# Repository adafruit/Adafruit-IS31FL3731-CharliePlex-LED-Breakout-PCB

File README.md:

## Adafruit IS31FL3731 CharliePlex LED Breakout PCB
<a href="http://www.adafruit.com/products/2946"><br/>
Click here to purchase one from the Adafruit shop</a>

The IS31FL3731 will let you get back to that classic LED matrix look, with a nice upgrade! This I2C LED driver chip has the ability to PWM each individual LED in a 16x9 grid so you can have beautiful LED lighting effects, without a lot of pin twiddling. Simply tell the chip which LED on the grid you want lit, and what brightness and it's all taken care of for you.

The IS31FL3731 is a nice little chip - it can use 2.7-5.5V power and logic so its flexible for use with any microcontroller. You can set the address so up to 4 matrices can share an I2C bus. Inside is enough RAM for 8 seperate frames of display memory so you can set up multiple frames of an animation and flip them to be displayed with a single command.

This chip is great for making small LED displays, and we even designed the breakout to match up with our ready-to-go LED grids in red, yellow, green, blue and white. Sandwich the driver and matrix breakout, solder together for a compact setup. Or you can DIY your own setup, just follow the LED grid schematic in the IS31FL3731 datasheet.

To get you going fast, we spun up a custom-made PCB in the STEMMA QT form factor, making it easy to interface with. The STEMMA QT connectors on either side are compatible with the SparkFun Qwiic I2C connectors. This allows you to make solderless connections between your development board and the IS31FL3731 or to chain it with a wide range of other sensors and accessories using a compatible cable. The IS31 is compatible with 3-5V power and logic, so it's ready to go with just about any microcontroller or microcomputer board!

Please note this does not come with any LEDs, you can pick up a matching LED matrix from us or DIY your own.

Pick up a driver board and your favorite color LEDs to match. You'll need to do some basic soldering to attach the driver backpack and matrix together, and run wires to your microcontroller, but its not too hard. Then install our Arduino or CircuitPython libraries to get some LEDs blinking immediately. Our library is Adafruit_GFX compatible so you can draw lines, circles, text, and small bitmaps if you want more graphics control

Check out our detailed tutorial for Arduino & CircuitPython support, pinouts, assembly, wiring, and more!

See the following products for various flavors of this product:

- https://www.adafruit.com/products/2946 (the IS31FL breakout)
- https://www.adafruit.com/products/2973 (blue LEDs)
- https://www.adafruit.com/products/2974 (cool white LEDs)
- https://www.adafruit.com/products/2948 (yellow LEDs)
- https://www.adafruit.com/products/2947 (red LEDs)
- https://www.adafruit.com/products/2972 (green LEDs)

PCB files for the IS31FL3731 CharliePlex LED Breakouts. The format is EagleCAD schematic and board layout

### License

Adafruit invests time and resources providing this open source design, please support Adafruit and open-source hardware by purchasing products from [Adafruit](https://www.adafruit.com)!

All text above must be included in any redistribution

Designed by Limor Fried/Ladyada for Adafruit Industries.
Creative Commons Attribution/Share-Alike, all text above must be included in any redistribution. 
See license.txt for additional information.

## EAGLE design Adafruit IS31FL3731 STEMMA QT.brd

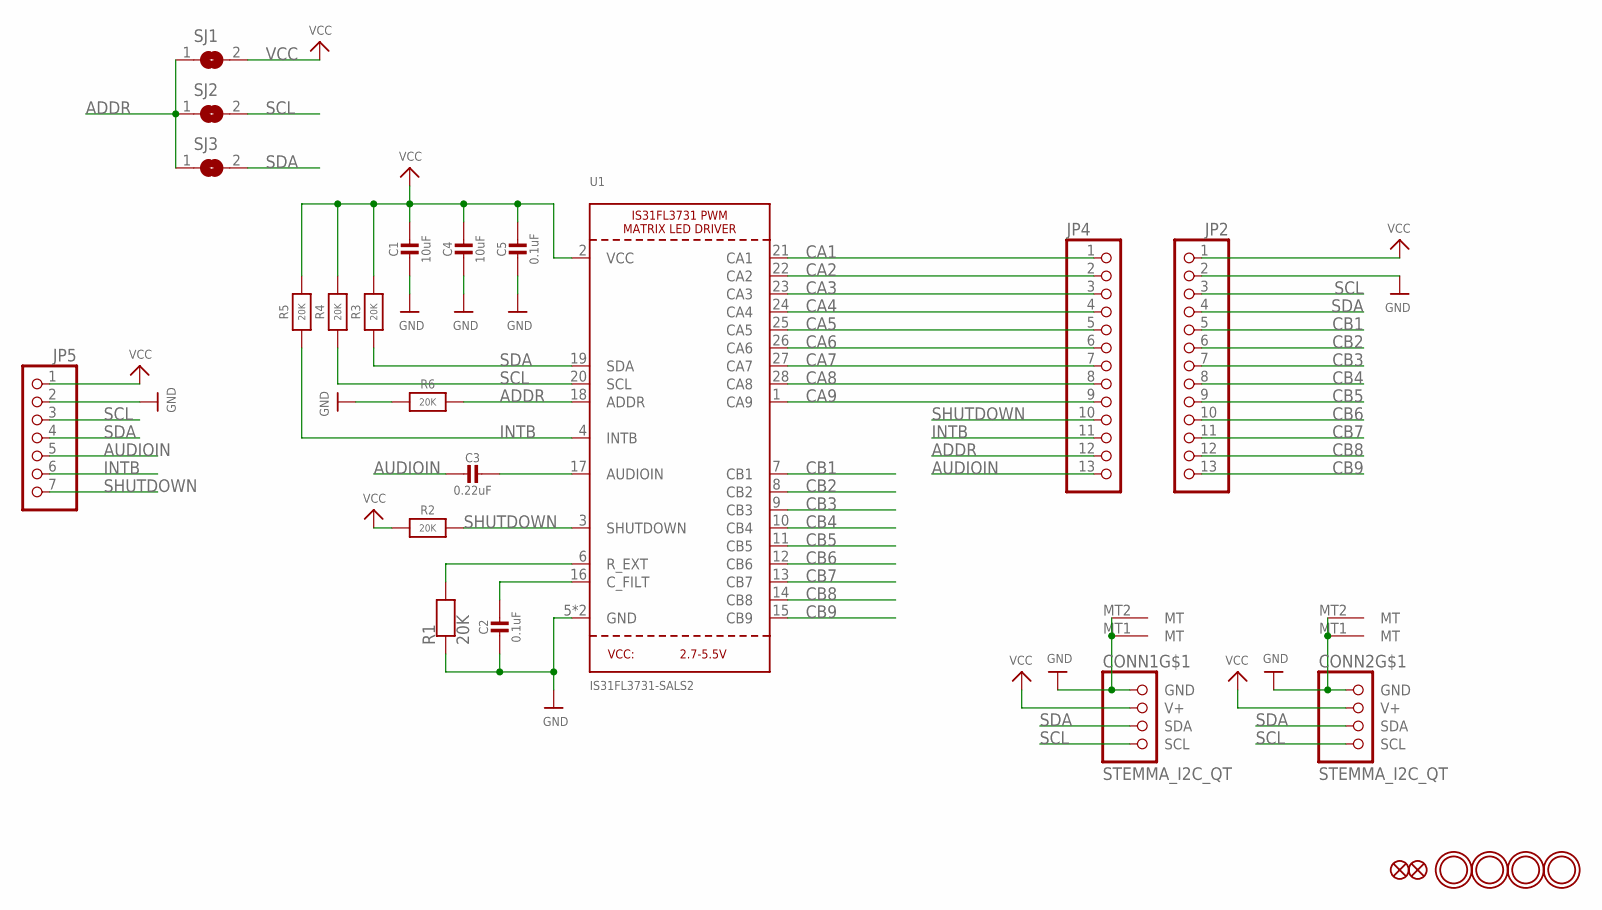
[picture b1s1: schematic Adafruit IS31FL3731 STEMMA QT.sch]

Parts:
C1, C4: 10uF; 0805-NO
C2, C5: 0.1uF; 0603-NO
C3: 0.22uF; 0603-NO
CONN1, CONN2: STEMMA_I2C_QT; JST_SH4
FID1, FID2: FIDUCIAL_1MM
JP2, JP4: HEADER-1X13; 1X13_ROUND_70
JP5: HEADER-1X7THICKER; 1X07_ROUND_76
R1: 20K; 0603-THM
R2, R3, R4, R5, R6: 20K; 0603-NO
SJ1, SJ2, SJ3: SOLDERJUMPER; SOLDERJUMPER_ARROW_NOPASTE
U1: IS31FL3731-SALS2; QFN28_4MM_0.4MM
U$3, U$4, U$5, U$6: MOUNTINGHOLE2.5; MOUNTINGHOLE_2.5_PLATED

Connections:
ADDR: JP4.12, R6.2, SJ1.1, SJ2.1, SJ3.1, U1.18 (ADDR)
AUDIOIN: C3.2, JP4.13, JP5.5
CA1: JP4.1, U1.21 (CA1)
CA2: JP4.2, U1.22 (CA2)
CA3: JP4.3, U1.23 (CA3)
CA4: JP4.4, U1.24 (CA4)
CA5: JP4.5, U1.25 (CA5)
CA6: JP4.6, U1.26 (CA6)
CA7: JP4.7, U1.27 (CA7)
CA8: JP4.8, U1.28 (CA8)
CA9: JP4.9, U1.1 (CA9)
CB1: JP2.5, U1.7 (CB1)
CB2: JP2.6, U1.8 (CB2)
CB3: JP2.7, U1.9 (CB3)
CB4: JP2.8, U1.10 (CB4)
CB5: JP2.9, U1.11 (CB5)
CB6: JP2.10, U1.12 (CB6)
CB7: JP2.11, U1.13 (CB7)
CB8: JP2.12, U1.14 (CB8)
CB9: JP2.13, U1.15 (CB9)
GND: C1.2, C2.2, C4.2, C5.2, CONN1.1 (GND), CONN1.MT1 (MT), CONN1.MT2 (MT), CONN2.1 (GND), CONN2.MT1 (MT), CONN2.MT2 (MT), JP2.2, JP5.2, R1.1, R1.11 (1), R6.1, U1.5 (GND), U1.THERMAL (GND)
INTB: JP4.11, JP5.6, R5.1, U1.4 (INTB)
unnamed: C2.1, U1.16 (C_FILT)
unnamed: C3.1, U1.17 (AUDIOIN)
REXT: R1.2, R1.22 (2), U1.6 (R_EXT)
SCL: CONN1.4 (SCL), CONN2.4 (SCL), JP2.3, JP5.3, R4.1, SJ2.2, U1.20 (SCL)
SDA: CONN1.3 (SDA), CONN2.3 (SDA), JP2.4, JP5.4, R3.1, SJ3.2, U1.19 (SDA)
SHUTDOWN: JP4.10, JP5.7, R2.2, U1.3 (SHUTDOWN)
VCC: C1.1, C4.1, C5.1, CONN1.2 (V+), CONN2.2 (V+), JP2.1, JP5.1, R2.1, R3.2, R4.2, R5.2, SJ1.2, U1.2 (VCC)

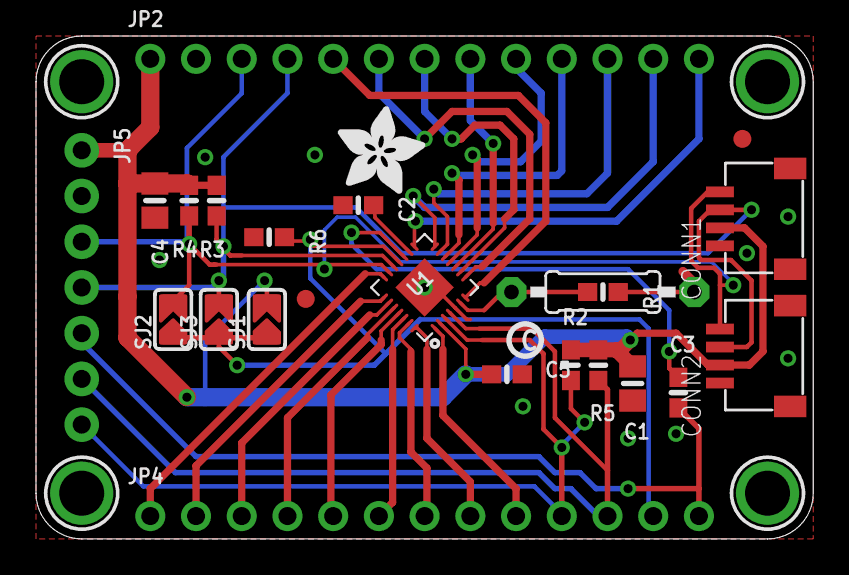
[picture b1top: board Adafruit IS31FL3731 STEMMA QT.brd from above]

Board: 2 copper layers, 43.2 x 27.9 mm, 68 parts (0 on the bottom side), 29 nets.

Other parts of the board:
PLABEL0: PLABEL0
PLABEL1: PLABEL1
PLABEL2: PLABEL2
PLABEL3: PLABEL3
PLABEL4: PLABEL4
PLABEL5: PLABEL5
PLABEL6: PLABEL6
PLABEL7: PLABEL7
PLABEL8: PLABEL8
PLABEL9: PLABEL9
PLABEL10: PLABEL10
PLABEL11: PLABEL11
PLABEL12: PLABEL12
PLABEL13: PLABEL13
PLABEL14: PLABEL14
PLABEL15: PLABEL15
PLABEL16: PLABEL16
PLABEL17: PLABEL17
PLABEL18: PLABEL18
PLABEL19: PLABEL19
PLABEL20: PLABEL20
PLABEL21: PLABEL21
PLABEL22: PLABEL22
PLABEL23: PLABEL23
PLABEL24: PLABEL24
PLABEL25: PLABEL25
PLABEL26: PLABEL26
PLABEL27: PLABEL27
PLABEL28: PLABEL28
PLABEL29: PLABEL29
PLABEL30: PLABEL30
PLABEL31: PLABEL31
PLABEL32: PLABEL32
PLABEL33: PLABEL33
PLABEL34: PLABEL34
PLABEL35: PLABEL35
PLABEL36: PLABEL36
PLABEL37: PLABEL37
PLABEL38: PLABEL38
PLABEL39: PLABEL39
U$10: ADAFRUIT_5MM
U$11: PCBFEAT-REV-040

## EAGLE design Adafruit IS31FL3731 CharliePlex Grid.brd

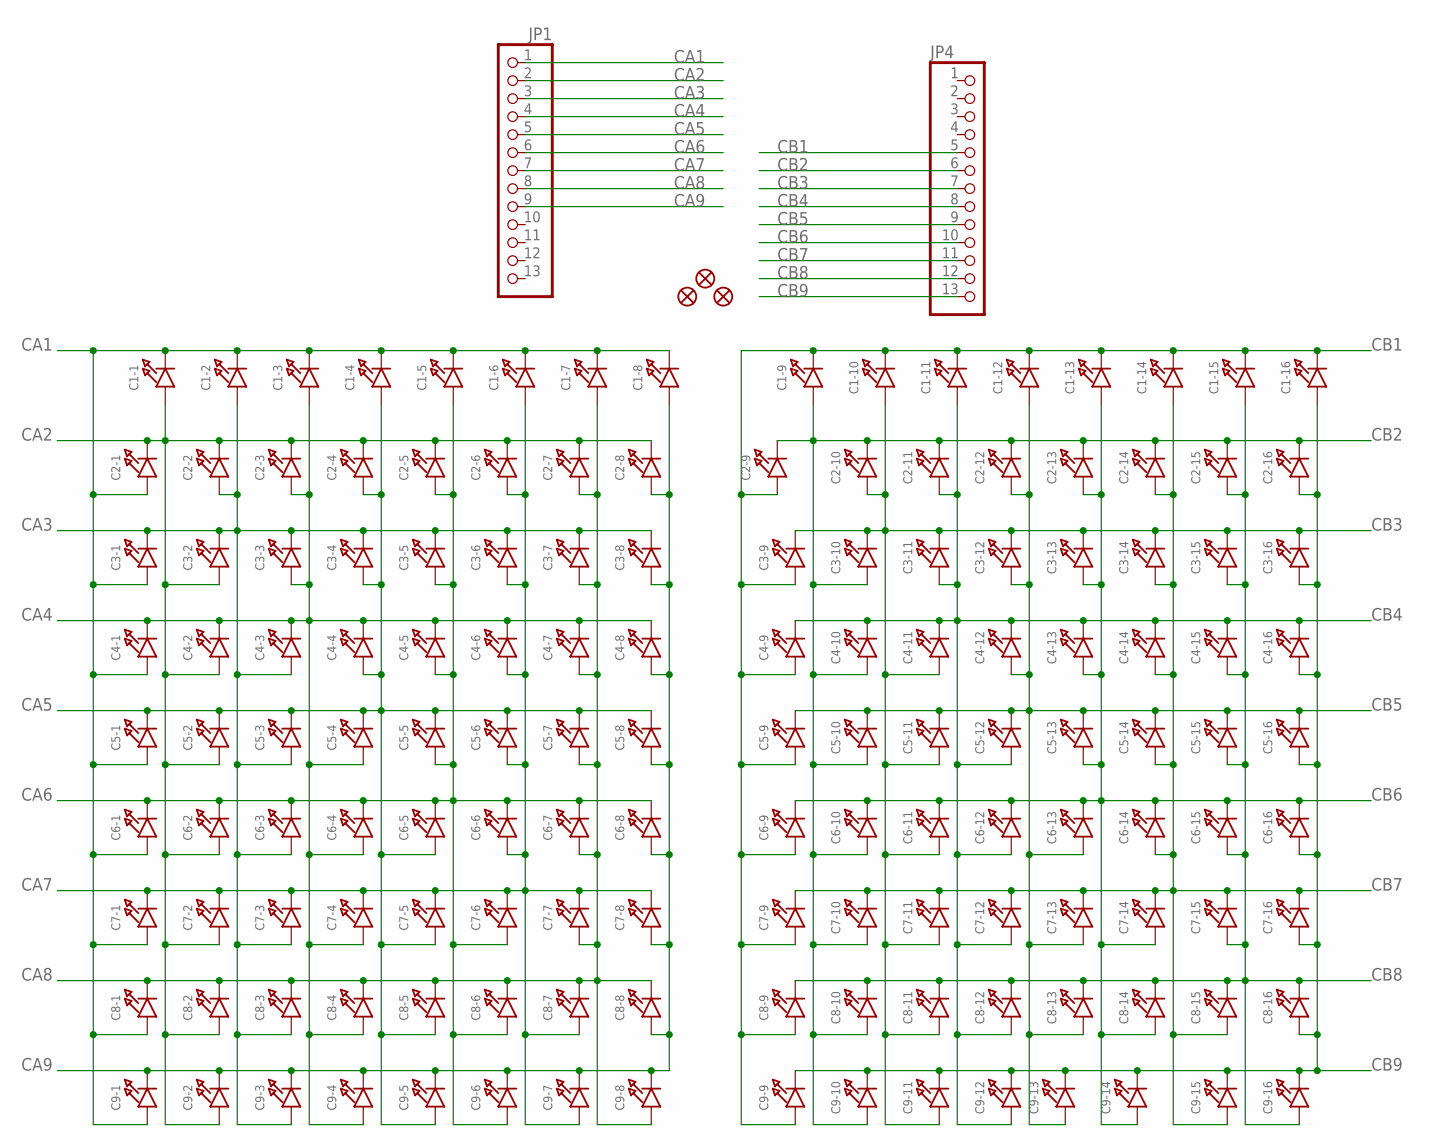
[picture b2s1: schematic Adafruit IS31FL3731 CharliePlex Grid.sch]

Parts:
C1-1, C1-2, C1-3, C1-4, C1-5, C1-6, C1-7, C1-8, C1-9, C1-10, C1-11, C1-12, C1-13, C1-14, C1-15, C1-16, C2-1, C2-2, C2-3, C2-4, C2-5, C2-6, C2-7, C2-8, C2-9, C2-10, C2-11, C2-12, C2-13, C2-14, C2-15, C2-16, C3-1, C3-2, C3-3, C3-4, C3-5, C3-6, C3-7, C3-8, C3-9, C3-10, C3-11, C3-12, C3-13, C3-14, C3-15, C3-16, C4-1, C4-2, C4-3, C4-4, C4-5, C4-6, C4-7, C4-8, C4-9, C4-10, C4-11, C4-12, C4-13, C4-14, C4-15, C4-16, C5-1, C5-2, C5-3, C5-4, C5-5, C5-6, C5-7, C5-8, C5-9, C5-10, C5-11, C5-12, C5-13, C5-14, C5-15, C5-16, C6-1, C6-2, C6-3, C6-4, C6-5, C6-6, C6-7, C6-8, C6-9, C6-10, C6-11, C6-12, C6-13, C6-14, C6-15, C6-16, C7-1, C7-2, C7-3, C7-4, C7-5, C7-6, C7-7, C7-8, C7-9, C7-10, C7-11, C7-12, C7-13, C7-14, C7-15, C7-16, C8-1, C8-2, C8-3, C8-4, C8-5, C8-6, C8-7, C8-8, C8-9, C8-10, C8-11, C8-12, C8-13, C8-14, C8-15, C8-16, C9-1, C9-2, C9-3, C9-4, C9-5, C9-6, C9-7, C9-8, C9-9, C9-10, C9-11, C9-12, C9-13, C9-14, C9-15, C9-16: LED0603_NOOUTLINE; CHIPLED_0603_NOOUTLINE
FID1, FID2, FID3: FIDUCIAL""; FIDUCIAL_1MM
JP1, JP4: HEADER-1X13; 1X13_ROUND_70

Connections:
CA1: C1-1.C, C1-2.C, C1-3.C, C1-4.C, C1-5.C, C1-6.C, C1-7.C, C1-8.C, C2-1.A, C3-1.A, C4-1.A, C5-1.A, C6-1.A, C7-1.A, C8-1.A, C9-1.A, JP1.1
CA2: C1-1.A, C2-1.C, C2-2.C, C2-3.C, C2-4.C, C2-5.C, C2-6.C, C2-7.C, C2-8.C, C3-2.A, C4-2.A, C5-2.A, C6-2.A, C7-2.A, C8-2.A, C9-2.A, JP1.2
CA3: C1-2.A, C2-2.A, C3-1.C, C3-2.C, C3-3.C, C3-4.C, C3-5.C, C3-6.C, C3-7.C, C3-8.C, C4-3.A, C5-3.A, C6-3.A, C7-3.A, C8-3.A, C9-3.A, JP1.3
CA4: C1-3.A, C2-3.A, C3-3.A, C4-1.C, C4-2.C, C4-3.C, C4-4.C, C4-5.C, C4-6.C, C4-7.C, C4-8.C, C5-4.A, C6-4.A, C7-4.A, C8-4.A, C9-4.A, JP1.4
CA5: C1-4.A, C2-4.A, C3-4.A, C4-4.A, C5-1.C, C5-2.C, C5-3.C, C5-4.C, C5-5.C, C5-6.C, C5-7.C, C5-8.C, C6-5.A, C7-5.A, C8-5.A, C9-5.A, JP1.5
CA6: C1-5.A, C2-5.A, C3-5.A, C4-5.A, C5-5.A, C6-1.C, C6-2.C, C6-3.C, C6-4.C, C6-5.C, C6-6.C, C6-7.C, C6-8.C, C7-6.A, C8-6.A, C9-6.A, JP1.6
CA7: C1-6.A, C2-6.A, C3-6.A, C4-6.A, C5-6.A, C6-6.A, C7-1.C, C7-2.C, C7-3.C, C7-4.C, C7-5.C, C7-6.C, C7-7.C, C7-8.C, C8-7.A, C9-7.A, JP1.7
CA8: C1-7.A, C2-7.A, C3-7.A, C4-7.A, C5-7.A, C6-7.A, C7-7.A, C8-1.C, C8-2.C, C8-3.C, C8-4.C, C8-5.C, C8-6.C, C8-7.C, C8-8.C, C9-8.A, JP1.8
CA9: C1-8.A, C2-8.A, C3-8.A, C4-8.A, C5-8.A, C6-8.A, C7-8.A, C8-8.A, C9-1.C, C9-2.C, C9-3.C, C9-4.C, C9-5.C, C9-6.C, C9-7.C, C9-8.C, JP1.9
CB1: C1-9.C, C1-10.C, C1-11.C, C1-12.C, C1-13.C, C1-14.C, C1-15.C, C1-16.C, C2-9.A, C3-9.A, C4-9.A, C5-9.A, C6-9.A, C7-9.A, C8-9.A, C9-9.A, JP4.5
CB2: C1-9.A, C2-9.C, C2-10.C, C2-11.C, C2-12.C, C2-13.C, C2-14.C, C2-15.C, C2-16.C, C3-10.A, C4-10.A, C5-10.A, C6-10.A, C7-10.A, C8-10.A, C9-10.A, JP4.6
CB3: C1-10.A, C2-10.A, C3-9.C, C3-10.C, C3-11.C, C3-12.C, C3-13.C, C3-14.C, C3-15.C, C3-16.C, C4-11.A, C5-11.A, C6-11.A, C7-11.A, C8-11.A, C9-11.A, JP4.7
CB4: C1-11.A, C2-11.A, C3-11.A, C4-9.C, C4-10.C, C4-11.C, C4-12.C, C4-13.C, C4-14.C, C4-15.C, C4-16.C, C5-12.A, C6-12.A, C7-12.A, C8-12.A, C9-12.A, JP4.8
CB5: C1-12.A, C2-12.A, C3-12.A, C4-12.A, C5-9.C, C5-10.C, C5-11.C, C5-12.C, C5-13.C, C5-14.C, C5-15.C, C5-16.C, C6-13.A, C7-13.A, C8-13.A, C9-13.A, JP4.9
CB6: C1-13.A, C2-13.A, C3-13.A, C4-13.A, C5-13.A, C6-9.C, C6-10.C, C6-11.C, C6-12.C, C6-13.C, C6-14.C, C6-15.C, C6-16.C, C7-14.A, C8-14.A, C9-14.A, JP4.10
CB7: C1-14.A, C2-14.A, C3-14.A, C4-14.A, C5-14.A, C6-14.A, C7-9.C, C7-10.C, C7-11.C, C7-12.C, C7-13.C, C7-14.C, C7-15.C, C7-16.C, C8-15.A, C9-15.A, JP4.11
CB8: C1-15.A, C2-15.A, C3-15.A, C4-15.A, C5-15.A, C6-15.A, C7-15.A, C8-9.C, C8-10.C, C8-11.C, C8-12.C, C8-13.C, C8-14.C, C8-15.C, C8-16.C, C9-16.A, JP4.12
CB9: C1-16.A, C2-16.A, C3-16.A, C4-16.A, C5-16.A, C6-16.A, C7-16.A, C8-16.A, C9-9.C, C9-10.C, C9-11.C, C9-12.C, C9-13.C, C9-14.C, C9-15.C, C9-16.C, JP4.13

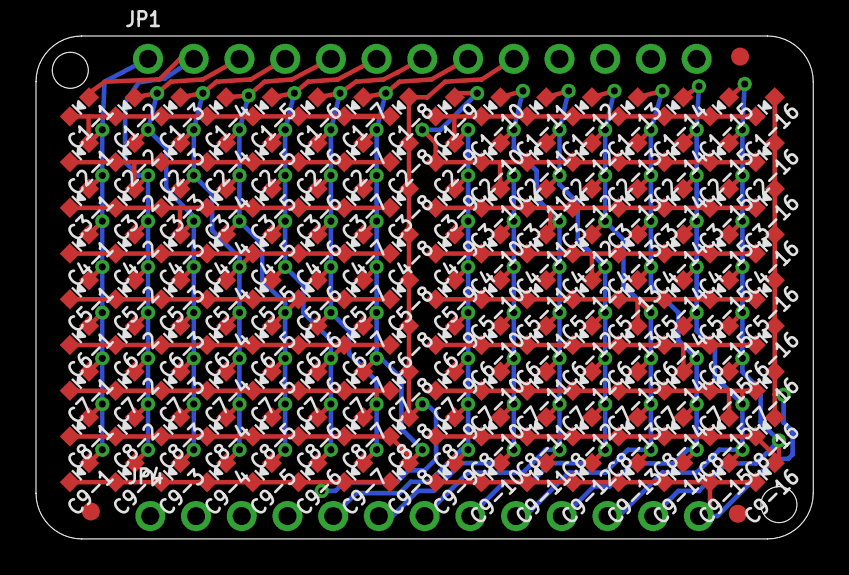
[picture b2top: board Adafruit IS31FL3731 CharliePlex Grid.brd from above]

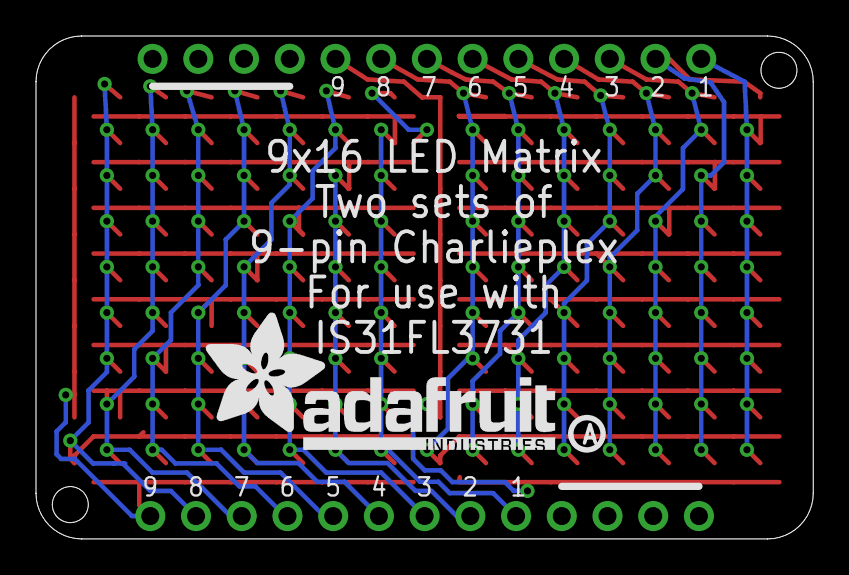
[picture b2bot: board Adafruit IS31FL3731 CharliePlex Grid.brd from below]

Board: 2 copper layers, 43.2 x 27.9 mm, 151 parts (2 on the bottom side), 18 nets.

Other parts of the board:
U$1: PCBFEAT-REV-040
U$2: ADAFRUIT_TEXT_20MM

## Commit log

2016-06-20 init-plex
2022-12-21 Adding STEMMA QT files
2022-12-21 Updating measures

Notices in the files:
parts and their libraries:
microbuilder: This work is placed in the public domain, and may be freely used for commercial and non-commercial work with the following conditions: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
